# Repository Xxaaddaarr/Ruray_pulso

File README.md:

# Ruray_pulso
Respositorio de archivos para el proyecto de pulsioximetría

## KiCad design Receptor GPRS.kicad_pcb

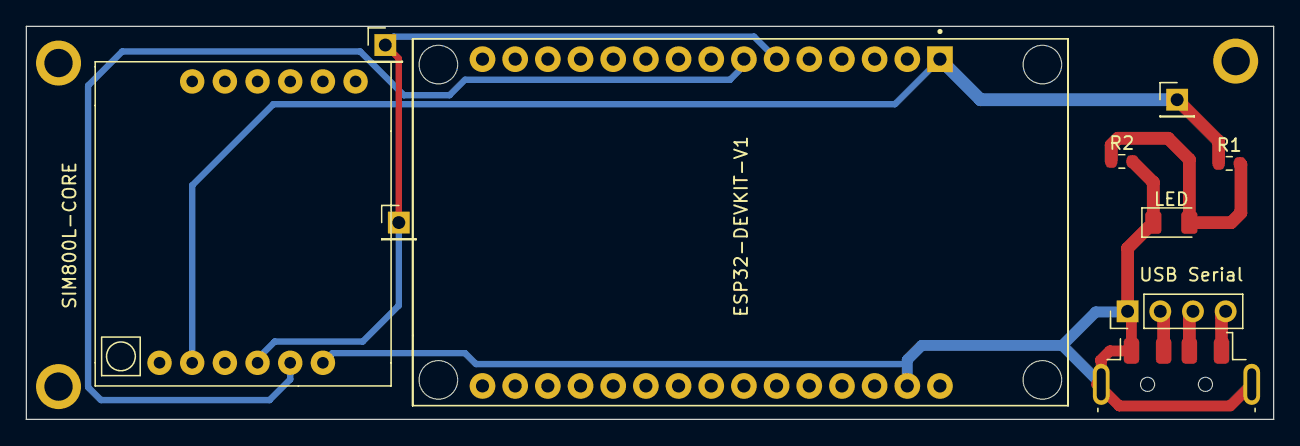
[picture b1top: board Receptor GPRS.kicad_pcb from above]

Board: 2 copper layers, 96.9 x 30.5 mm, 6 parts (0 on the bottom side), 5 nets.

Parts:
ESP32-DEVKIT-V1: ESP32-DEVKIT-V1; MODULE_ESP32_DEVKIT_V1
LED: LED Azul 3.5V; LED_1206_3216Metric
R1: 220 Ohms; R_0603_1608Metric
R2: 1000 Ohms; R_0603_1608Metric
SIM800L-CORE: SIM800L-CORE
USB Serial: USB_A; USB_A_Molex_48037-2200_Horizontal

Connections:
Earth: ESP32-DEVKIT-V1.29 (GND), LED.1 (K), R2.2, SIM800L-CORE.6 (GND), USB Serial.4 (GND), USB Serial.5 (Shield)
unnamed: LED.2 (A), R1.2, R2.1
unnamed: ESP32-DEVKIT-V1.6 (RX2), SIM800L-CORE.4 (RXD)
unnamed: ESP32-DEVKIT-V1.7 (TX2), SIM800L-CORE.5 (TXD)
unnamed: ESP32-DEVKIT-V1.1 (3V3), R1.1, SIM800L-CORE.2 (VCC)

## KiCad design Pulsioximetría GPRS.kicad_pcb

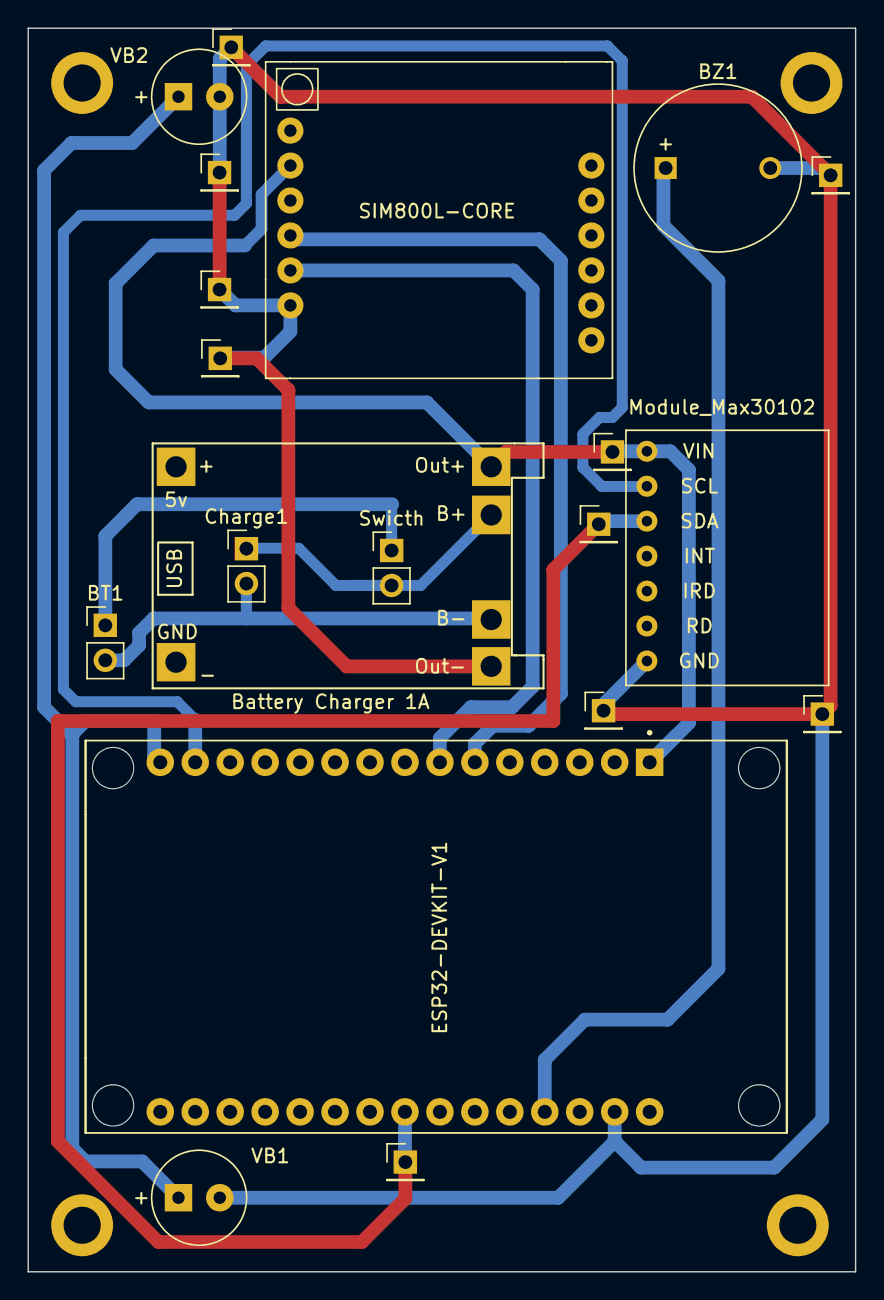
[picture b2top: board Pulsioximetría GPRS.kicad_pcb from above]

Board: 2 copper layers, 60.1 x 90.4 mm, 10 parts (0 on the bottom side), 11 nets.

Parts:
BT1: Battery_Cell; PinHeader_1x02_P2.54mm_Vertical
BZ1: Buzzer; MagneticBuzzer_ProSignal_ABI-010-RC
Charge1: PinHeader_1x02_P2.54mm_Vertical
ESP32-DEVKIT-V1: ESP32-DEVKIT-V1; MODULE_ESP32_DEVKIT_V1
Module_Max30102: module_max30102
SIM800L-CORE: SIM800L-CORE
Swicth: SW_DIP_x01; PinHeader_1x02_P2.54mm_Vertical
U4: TP4056-18650
VB1, VB2: Vibrator; MagneticBuzzer_Kobitone_254-EMB73-RO

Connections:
Earth: BZ1.2 (+), ESP32-DEVKIT-V1.29 (GND), Module_Max30102.7 (GND), SIM800L-CORE.6 (GND), U4.4 (Out-), VB1.2 (+), VB2.2 (+)
unnamed: BT1.1 (+), Swicth.1
unnamed: BT1.2 (-), Charge1.2 (-), U4.6 (B-)
unnamed: BZ1.1 (-), ESP32-DEVKIT-V1.27 (D12)
unnamed: Charge1.1 (+), Swicth.2, U4.5 (B+)
unnamed: ESP32-DEVKIT-V1.1 (3V3), Module_Max30102.1 (VIN), SIM800L-CORE.2 (VCC), U4.3 (Out+)
unnamed: ESP32-DEVKIT-V1.14 (D22), Module_Max30102.2 (SCL)
unnamed: ESP32-DEVKIT-V1.15 (D23), VB1.1 (-), VB2.1 (-)
unnamed: ESP32-DEVKIT-V1.23 (D25), Module_Max30102.3 (SDA)
unnamed: ESP32-DEVKIT-V1.6 (RX2), SIM800L-CORE.4 (RXD)
unnamed: ESP32-DEVKIT-V1.7 (TX2), SIM800L-CORE.5 (TXD)
